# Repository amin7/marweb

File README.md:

# WebDAV_air
SdFat from esp lib
https://github.com/ardyesp/ESPWebDAV.git
https://arduinojson.org/v6/api/

SPIFFS 1MB
#Pins

Pin |   Function  | ESP-8266 Pin| used
TX  |   TXD       |     TXD|
RX  |   RXD       |     RXD|
A0  |   Analog input, max 3.3V input| 
D0  |   IO        | GPIO16|
D1  |   IO, SCL   | GPIO5|
D2  |   IO, SDA   | GPIO4|
D3  |   IO, 10k Pull-up|    GPIO0|
D4  |   IO, 10k Pull-up, BUILTIN_LED|   GPIO2| 
D5  |   IO, SCK   | GPIO14|
D6  |   IO, MISO  | GPIO12|relay
D7  |   IO, MOSI  | GPIO13|
D8  |   IO, 10k Pull-down, SS|  GPIO15|
G   |   Ground    | GND|
5V  |   5V        | -   |
3V3 |   3.3V      | 3.3V|
RST |   Reset     | RST |

card
1 (no wire)
2 CS (D1,D2)
3 MOSI (D7)
4 3.3v
5 SCK (D5)
6 GND
7 MISO (D6)
8

connector
1 GND 
2 card detect <470> (D0)-(GND if inserted)
3 MISO (D6) 
4 SCK  <1k> (D5)
5 3.3 v
6 MOSI <1k> (D7)
7 CS  <1k> (D1,D2)
---------
8 RX <470>RX<1k>GND
9 TX TX

[eclipse launch target]
board: D1 R2 & mini
CPU 160
VTable IRAM
Flash 4MB FS 2MB

[gtest]
https://github.com/google/googletest.git

To access the drive from Windows, type `\\192.168.1.106@8080\DavWWWRoot` at the Run prompt, or use Map Network Drive menu in Windows Explorer
#pecondition
put config.json in fd root folder
 { 'ssid':...,'pwd':...,'hostname':...,'mode':..}"
 mode= [WIFI_OFF = 0, WIFI_STA = 1, WIFI_AP = 2]
 
 testweb.py  -c ./webconfig.json
 
 CFrontendFS.py ../frontend/SPIFFSdlg.html.gz
 
 #create spiffs bin file
 https://github.com/esp8266/arduino-esp8266fs-plugin/issues/51
 
 D:\personal\arduino\packages\esp8266\tools\mkspiffs\2.5.0-4-b40a506\mkspiffs.exe  -p 256 -b 8192 -s 1028096 -c spiffs spiffs.bin 
 D:\personal\arduino\packages\esp8266\hardware\esp8266\2.6.3\tools\esptool\esptool.py -c esp8266 -b 921600 -p COM7 write_flash 0x200000 spiffs.bin
  
D:\user\workspace\arduinocdt\packages\esp8266\tools\mkspiffs\2.5.0-4-b40a506\mkspiffs.exe  -p 256 -b 8192 -s 1028096 -c spiffs spiffs.bin 
D:\user\workspace\arduinocdt\packages\esp8266\hardware\esp8266\2.6.2\tools\esptool\esptool.py -c esp8266 -b 921600 -p COM7 write_flash 0x200000 spiffs.bin

 ~/.platformio/packages/tool-mkspiffs/mkspiffs -p 256 -b 8192 -s 1028096 -c spiffs spiffs.bin
g++ -Wall -g -std=c++11 -DTEST CGcodeParser.cpp -o CGcodeParser 
 
 https://regex101.com/
 
./obj/unittests.exe --gtest_list_tests
./obj/unittests.exe --gtest_filter=CProbeAreaTest*
 
[todo]
lissen only  uart mode
pcb probe
send gcode on print with autoloevel correction
send status
web add cmd wait for end previous

/gcodeInfo?file=/SD/CFFFP_bedlevel.gcode
/probe?mode=once&zHop=1&feedRateZ=200&probeDistance=5&feedRateProbe=20&doubleTouch=0
/probe?mode=area&sizeX=50&sizeY=50&grid=10&levelDelta=1&feedRateXY=200&feedRateProbe=20&doubleTouch=0

run -e d1_mini
run --target upload -e d1_mini

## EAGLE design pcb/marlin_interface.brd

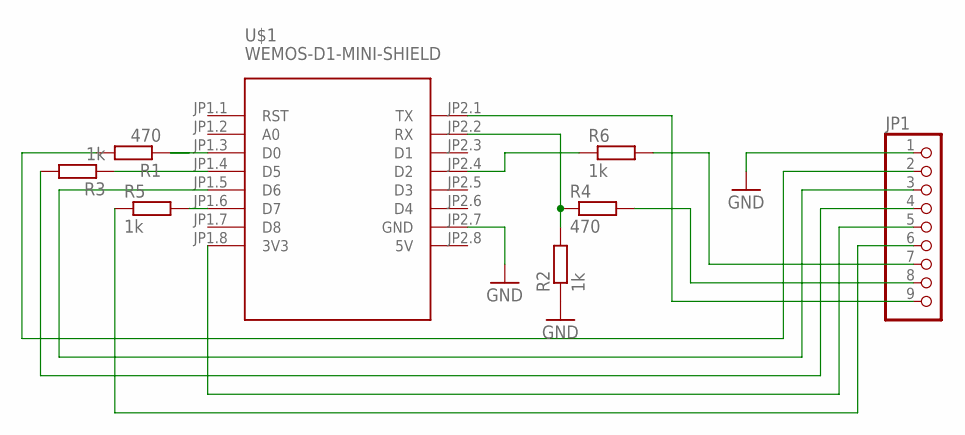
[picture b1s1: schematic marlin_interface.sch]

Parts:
JP1: PINHD-1X9/90; 1X09/90
R1, R4: 470; 0204/5
R2, R3, R5, R6: 1k; 0204/5
U$1: WEMOS-D1-MINI-SHIELD

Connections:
5V: U$1.JP2.8 (5V)
GND: JP1.1, R2.1, U$1.JP2.7 (GND)
unnamed: JP1.9, U$1.JP2.1 (TX)
unnamed: JP1.3, U$1.JP1.5 (D6)
unnamed: JP1.8, R4.2
unnamed: JP1.5, U$1.JP1.8 (3V3)
unnamed: JP1.2, R1.2
unnamed: R1.1, U$1.JP1.3 (D0)
unnamed: R2.2, R4.1, U$1.JP2.2 (RX)
unnamed: JP1.4, R3.2
unnamed: R5.2, U$1.JP1.6 (D7)
unnamed: JP1.6, R5.1
unnamed: R6.1, U$1.JP2.4 (D2)
unnamed: JP1.7, R6.2
unnamed: R3.1, U$1.JP1.4 (D5)

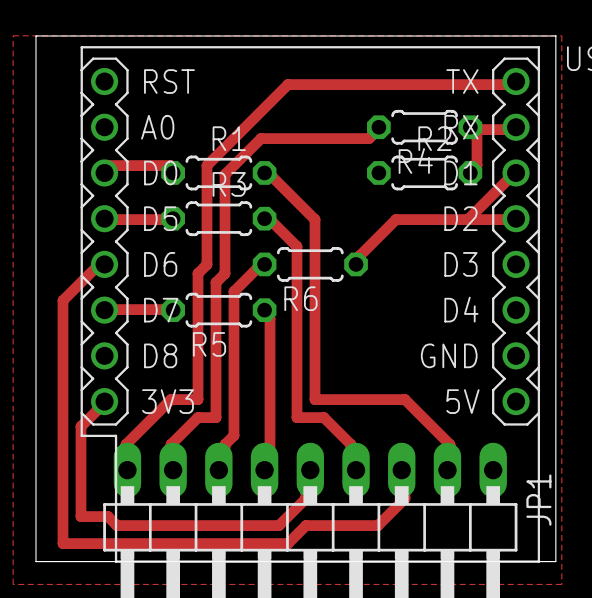
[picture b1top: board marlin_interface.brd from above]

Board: 2 copper layers, 28.9 x 29.2 mm, 8 parts (0 on the bottom side), 14 nets.

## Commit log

2020-03-11 initial
2020-03-11 fix warnings
2020-03-11 spifs upload
2020-03-11 fix hhtp upload
2020-03-11 fix probe
2020-03-12 probe vis
2020-03-12 upd probe on call back only
2020-03-18 use std ota
2020-03-18 u ui
2020-03-28 change sd condrol when print start
2020-04-03 upd g code, fix area
2020-04-04 fix autolevel
2020-04-04 add gtest to pio
2020-04-05 fix bed level
2020-04-06 tune on device
2020-04-23 cosm
2020-04-28 perform upd
2020-04-28 remove auto mode from sd
2020-05-03 upd ui
2020-05-06 fix linux buil
2020-05-09 network select from ui
2020-05-18 move multiple to be
2020-05-18 remove arduinJson

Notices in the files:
parts and their libraries:
diy-modules: Released under the Creative Commons Attribution 4.0 International License: http://creativecommons.org/licenses/by/4.0
